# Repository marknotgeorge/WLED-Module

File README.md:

# WLED-Module
A minimal ESP32-based module for controlling a strip of WS2812 (Neopixel) LEDs using WLED

## Features
- Just the components needed. Nothing more, nothing less.
- Programming header for use with a USB-UART dongle, with auto-reset circuitry for buttonless programming.
- Powered from a 5V power brick.

## To Do
- Add extra connector block to help power long strips.
- Add strapping resistor to EN pin.
- Add JLCPCB component codes to facilitate assembly.
- Layout PCB.
- Build it!

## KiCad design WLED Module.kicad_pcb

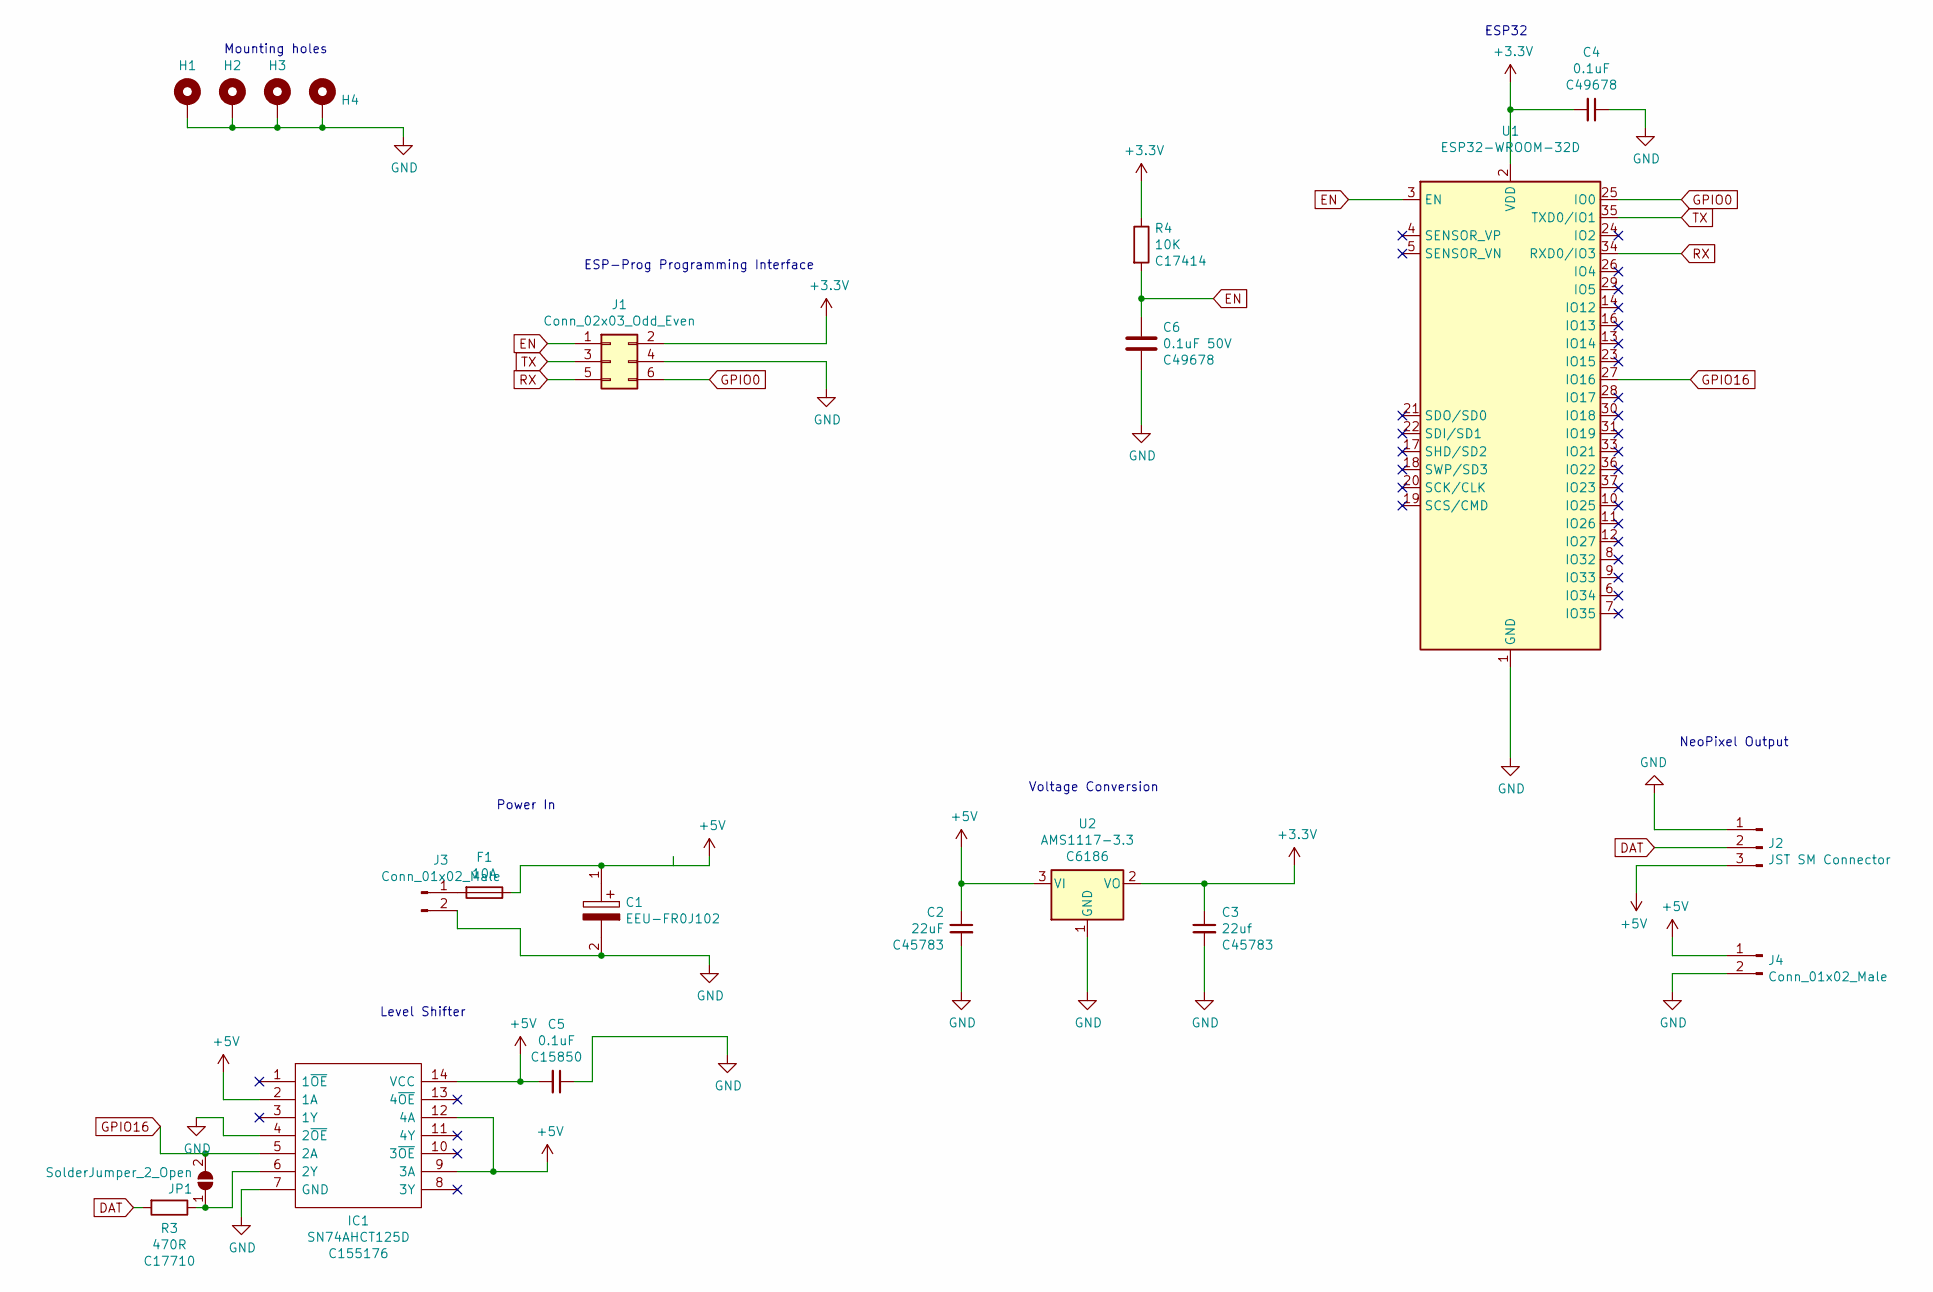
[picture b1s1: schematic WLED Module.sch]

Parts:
C1: EEU-FR0J102; CAPPRD350W65D800H1300; Manufacturer_Part_Number EEU-FR0J102; Mouser Part Number 667-EEU-FR0J102
C2: 22uF; C_0805_2012Metric_Pad1.15x1.40mm_HandSolder; LCSC C45783
C3: 22uf; C_0805_2012Metric_Pad1.15x1.40mm_HandSolder; LCSC C45783
C4: 0.1uF; C_0805_2012Metric_Pad1.15x1.40mm_HandSolder; LCSC C49678
C5: 0.1uF; C_0805_2012Metric_Pad1.15x1.40mm_HandSolder; LCSC C15850
C6: 0.1uF 50V; C_0805_2012Metric_Pad1.15x1.40mm_HandSolder; LCSC C49678
F1: 10A; Fuseholder_Blade_Mini_Keystone_3568
H1, H2, H3, H4: MountingHole_Pad; MountingHole_3.2mm_M3_DIN965_Pad
IC1: SN74AHCT125D; SOIC127P600X175-14N; Manufacturer_Part_Number SN74AHCT125D; Mouser Part Number 595-SN74AHCT125D
J1: Conn_02x03_Odd_Even; IDC-Header_2x03_P2.54mm_Vertical
J2: JST SM Connector; PinHeader_1x03_P2.54mm_Vertical
J3: Conn_01x02_Male; JST_VH_B2PS-VH_1x02_P3.96mm_Horizontal
J4: Conn_01x02_Male; PinHeader_1x02_P2.54mm_Vertical
JP1: SolderJumper_2_Open; SolderJumper-2_P1.3mm_Open_RoundedPad1.0x1.5mm
R3: 470R; R_0603_1608Metric_Pad1.05x0.95mm_HandSolder; LCSC C17710
R4: 10K; R_0805_2012Metric_Pad1.15x1.40mm_HandSolder; LCSC C17414
U1: ESP32-WROOM-32D; ESP32-WROOM-32
U2: AMS1117-3.3; SOT-223-3_TabPin2; LCSC C6186

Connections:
+3V3: C3.1, C4.2, J1.2, R4.1, U1.2 (VDD), U2.2 (VO)
+5V: C1.1, C2.1, C5.2, F1.1, IC1.2 (1A), IC1.9 (3A), IC1.12 (4A), IC1.14 (VCC), J2.3, J4.1, U2.3 (VI)
DAT: J2.2, R3.2
EN: C6.1, J1.1, R4.2, U1.3 (EN)
GND: C1.2, C2.2, C3.2, C4.1, C5.1, C6.2, H1.1, H2.1, H3.1, H4.1, IC1.4 (2~OE), IC1.7 (GND), J1.4, J2.1, J3.2, J4.2, U1.1 (GND), U1.15 (GND), U1.38 (GND), U1.39 (GND), U2.1 (GND)
GPIO0: J1.6, U1.25 (IO0)
GPIO16: IC1.5 (2A), JP1.2 (B), U1.27 (IO16)
unnamed: F1.2, J3.1
unnamed: IC1.6 (2Y), JP1.1 (A), R3.1
RX: J1.5, U1.34 (RXD0/IO3)
TX: J1.3, U1.35 (TXD0/IO1)

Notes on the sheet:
Power In
Level Shifter
Voltage Conversion
NeoPixel Output
ESP32
Mounting holes
ESP-Prog Programming Interface

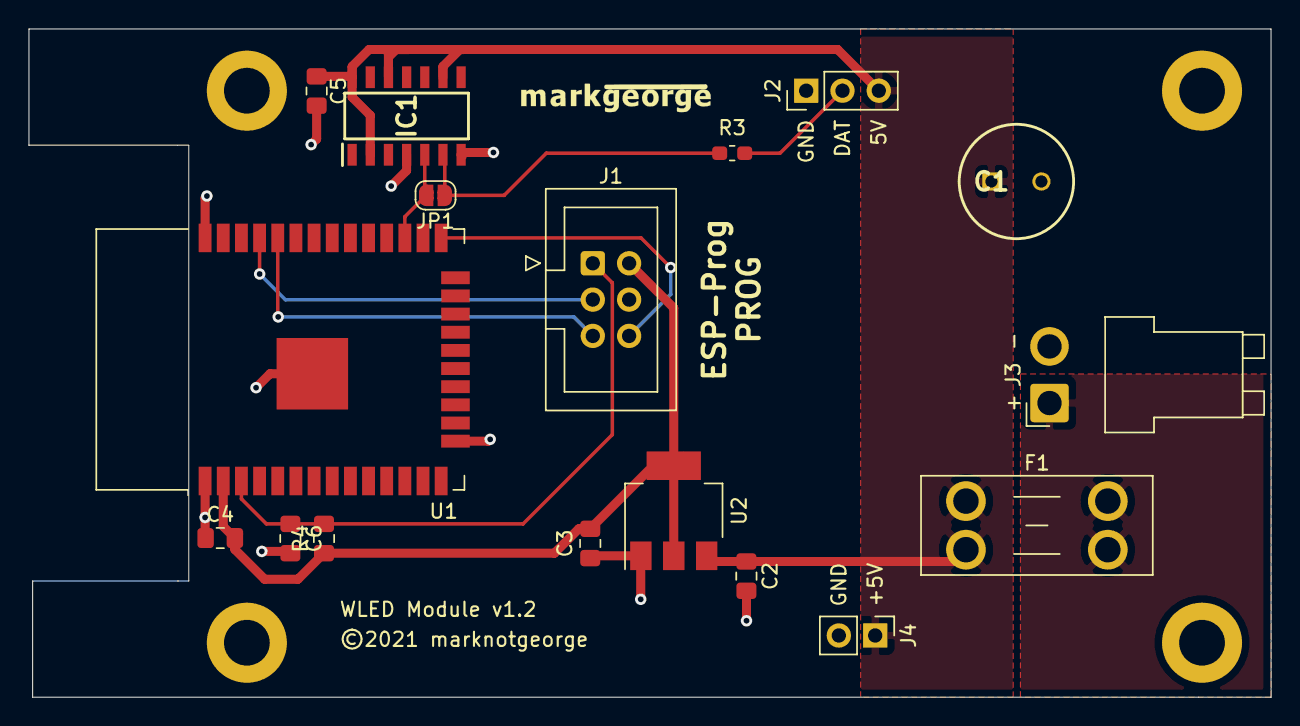
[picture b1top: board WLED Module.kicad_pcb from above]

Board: 2 copper layers, 86.9 x 46.7 mm, 21 parts (0 on the bottom side), 11 nets.

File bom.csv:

Comment,Designator,Footprint,LCSC
"EEU-FR0J102","C1","SamacSys:CAPPRD350W65D800H1300",""
"22uF","C2","Capacitor_SMD:C_0805_2012Metric_Pad1.15x1.40mm_HandSolder","C45783"
"22uf","C3","Capacitor_SMD:C_0805_2012Metric_Pad1.15x1.40mm_HandSolder","C45783"
"0.1uF","C4,C5","Capacitor_SMD:C_0805_2012Metric_Pad1.15x1.40mm_HandSolder","C49678"
"0.1uF 50V","C6","Capacitor_SMD:C_0805_2012Metric_Pad1.15x1.40mm_HandSolder","C49678"
"10A","F1","Fuse:Fuseholder_Blade_Mini_Keystone_3568",""
"MountingHole_Pad","H1,H2,H3,H4","MountingHole:MountingHole_3.2mm_M3_DIN965_Pad",""
"SN74AHCT125D","IC1","SamacSys:SOIC127P600X175-14N","C155176"
"Conn_02x03_Odd_Even","J1","Connector_IDC:IDC-Header_2x03_P2.54mm_Vertical",""
"JST SM Connector","J2","Connector_PinHeader_2.54mm:PinHeader_1x03_P2.54mm_Vertical",""
"Conn_01x02_Male","J3","Connector_JST:JST_VH_B2PS-VH_1x02_P3.96mm_Horizontal",""
"Conn_01x02_Male","J4","Connector_PinHeader_2.54mm:PinHeader_1x02_P2.54mm_Vertical",""
"SolderJumper_2_Open","JP1","Jumper:SolderJumper-2_P1.3mm_Open_RoundedPad1.0x1.5mm",""
"470R","R3","Resistor_SMD:R_0603_1608Metric_Pad1.05x0.95mm_HandSolder","C17710"
"10K","R4","Resistor_SMD:R_0805_2012Metric_Pad1.15x1.40mm_HandSolder","C17414"
"ESP32-WROOM-32D","U1","RF_Module:ESP32-WROOM-32",""
"AMS1117-3.3","U2","Package_TO_SOT_SMD:SOT-223-3_TabPin2","C6186"

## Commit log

2020-11-04 Initial commit (again)
2020-11-14 Various revisions:
    Input lines on IC1 tied to VCC.
    Input power connector changed to JST VH type.
    Decoupling capacitors changed to 0.1uf.
    Initial Gerber & other fab files generated.
2020-12-06 10A fuse added.
    BOM & Position file for JLCPCB added.
2021-02-10 V1.2
    * Auto-save circuitry replaced in favour of ESP-Prog interface.
    * Ancillary components rearranged.
2021-02-10 Create JLCPCB fabrication files
2021-02-10 Add the rest of the files. Duh.
2021-02-10 Adjustments for JLCPCB assembly.

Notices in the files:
WLED Module.kicad_pcb:
©2021 marknotgeorge
